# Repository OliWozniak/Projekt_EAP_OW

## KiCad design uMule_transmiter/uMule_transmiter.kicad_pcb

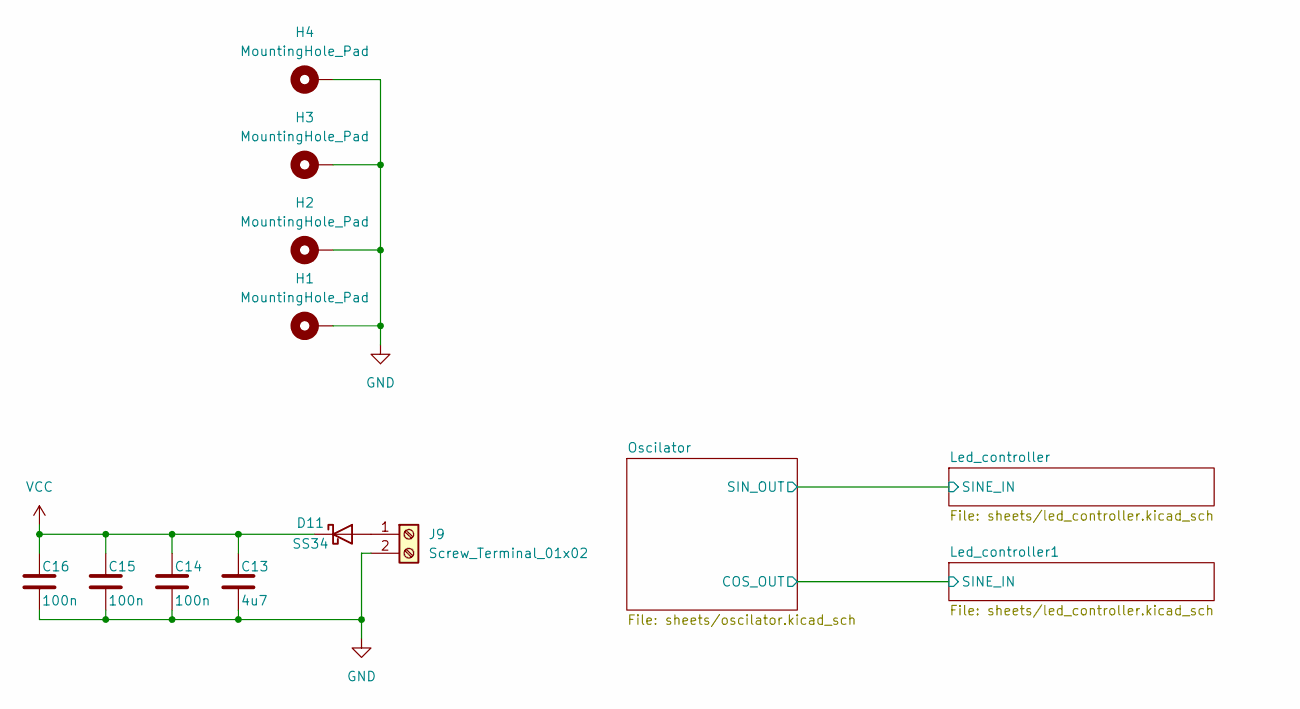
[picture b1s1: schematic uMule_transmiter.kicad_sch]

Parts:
C13: 4u7; C_0805_2012Metric
C14, C15, C16: 100n; C_0603_1608Metric_Pad1.08x0.95mm_HandSolder
D11: SS34; D_SMA
H1, H2, H3, H4: MountingHole_Pad; MountingHole_3.2mm_M3_Pad_Via
J9: Screw_Terminal_01x02; PhoenixContact_MCV_1,5_2-G-3.5_1x02_P3.50mm_Vertical

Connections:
GND: C13.2, C14.2, C15.2, C16.2, H1.1, H2.1, H3.1, H4.1, J9.2; also elsewhere on the board
unnamed: D11.2 (A), J9.1
VCC: C13.1, C14.1, C15.1, C16.1, D11.1 (K); also elsewhere on the board

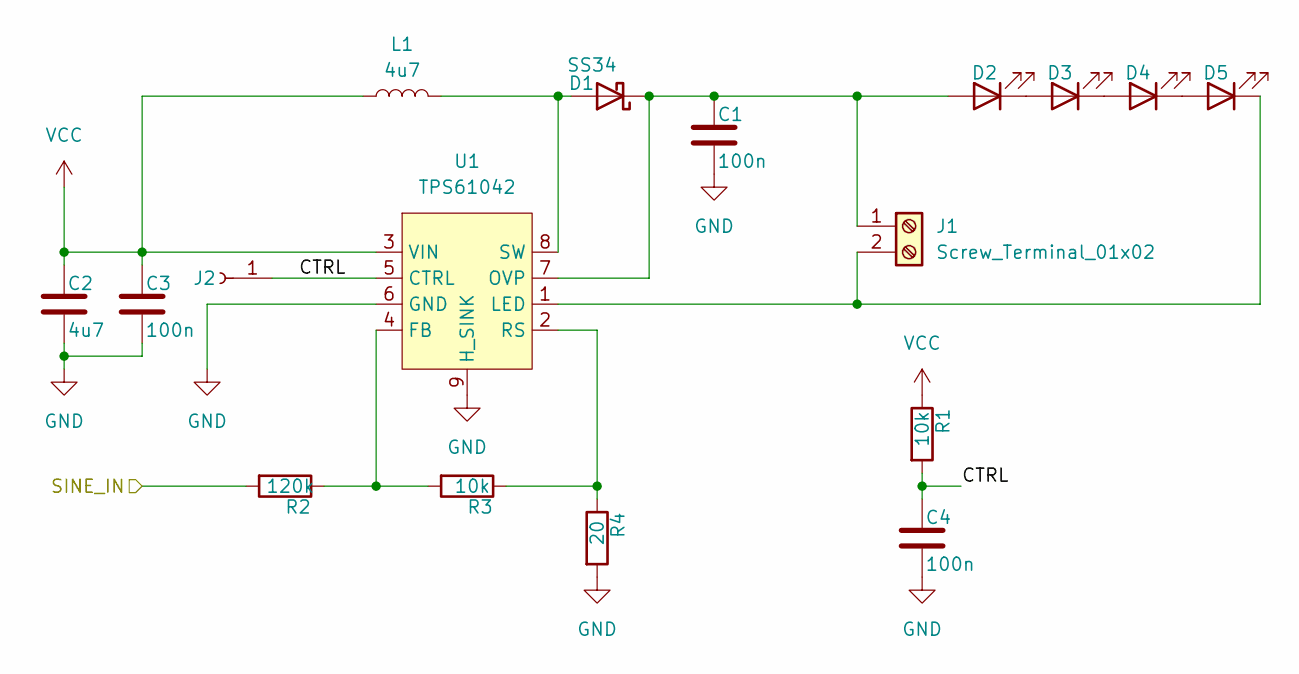
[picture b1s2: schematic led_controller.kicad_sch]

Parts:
C1, C3, C4: 100n; C_0603_1608Metric_Pad1.08x0.95mm_HandSolder
C2: 4u7; C_0805_2012Metric
D1: SS34; D_SMA
D2, D3, D4, D5: LED; LED_D5.0mm
J1: Screw_Terminal_01x02; PhoenixContact_MCV_1,5_2-G-3.5_1x02_P3.50mm_Vertical
J2: Conn_01x01_Socket; PinHeader_1x01_P2.54mm_Vertical
L1: 4u7; L_APV_ANR3015
R1, R3: 10k; R_0603_1608Metric_Pad0.98x0.95mm_HandSolder
R2: 120k; R_0603_1608Metric_Pad0.98x0.95mm_HandSolder
R4: 20; R_1206_3216Metric_Pad1.30x1.75mm_HandSolder
U1: TPS61042; Texas_S-PVSON-N8

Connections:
/Led_controller/CTRL: C4.1, J2.1, R1.2, U1.5 (CTRL)
/Led_controller/SINE_IN: R2.2; also elsewhere on the board
GND: C1.2, C2.2, C3.2, C4.2, R4.2, U1.6 (GND), U1.9 (H_SINK); also elsewhere on the board
unnamed: D1.2 (A), L1.2, U1.8 (SW)
unnamed: C1.1, D1.1 (K), D2.2 (A), J1.1, U1.7 (OVP)
unnamed: D2.1 (K), D3.2 (A)
unnamed: D3.1 (K), D4.2 (A)
unnamed: D4.1 (K), D5.2 (A)
unnamed: D5.1 (K), J1.2, U1.1 (LED)
unnamed: R2.1, R3.2, U1.4 (FB)
unnamed: R3.1, R4.1, U1.2 (RS)
VCC: C2.1, C3.1, L1.1, R1.1, U1.3 (VIN); also elsewhere on the board

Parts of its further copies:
C5, C7, C8: 100n; C_0603_1608Metric_Pad1.08x0.95mm_HandSolder
C6: 4u7; C_0805_2012Metric
D6: SS34; D_SMA
D7, D8, D9, D10: LED; LED_D5.0mm
J3: Screw_Terminal_01x02; PhoenixContact_MCV_1,5_2-G-3.5_1x02_P3.50mm_Vertical
J4: Conn_01x01_Socket; PinHeader_1x01_P2.54mm_Vertical
L2: 4u7; L_APV_ANR3015
R5, R7: 10k; R_0603_1608Metric_Pad0.98x0.95mm_HandSolder
R6: 120k; R_0603_1608Metric_Pad0.98x0.95mm_HandSolder
R8: 20; R_1206_3216Metric_Pad1.30x1.75mm_HandSolder
U2: TPS61042; Texas_S-PVSON-N8

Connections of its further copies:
/Led_controller1/CTRL: C8.1, J4.1, R5.2, U2.5 (CTRL)
/Led_controller1/SINE_IN: R6.2; also elsewhere on the board
GND: C5.2, C6.2, C7.2, C8.2, R8.2, U2.6 (GND), U2.9 (H_SINK); also elsewhere on the board
unnamed: D6.2 (A), L2.2, U2.8 (SW)
unnamed: C5.1, D6.1 (K), D7.2 (A), J3.1, U2.7 (OVP)
unnamed: D7.1 (K), D8.2 (A)
unnamed: D8.1 (K), D9.2 (A)
unnamed: D9.1 (K), D10.2 (A)
unnamed: D10.1 (K), J3.2, U2.1 (LED)
unnamed: R6.1, R7.2, U2.4 (FB)
unnamed: R7.1, R8.1, U2.2 (RS)
VCC: C6.1, C7.1, L2.1, R5.1, U2.3 (VIN); also elsewhere on the board

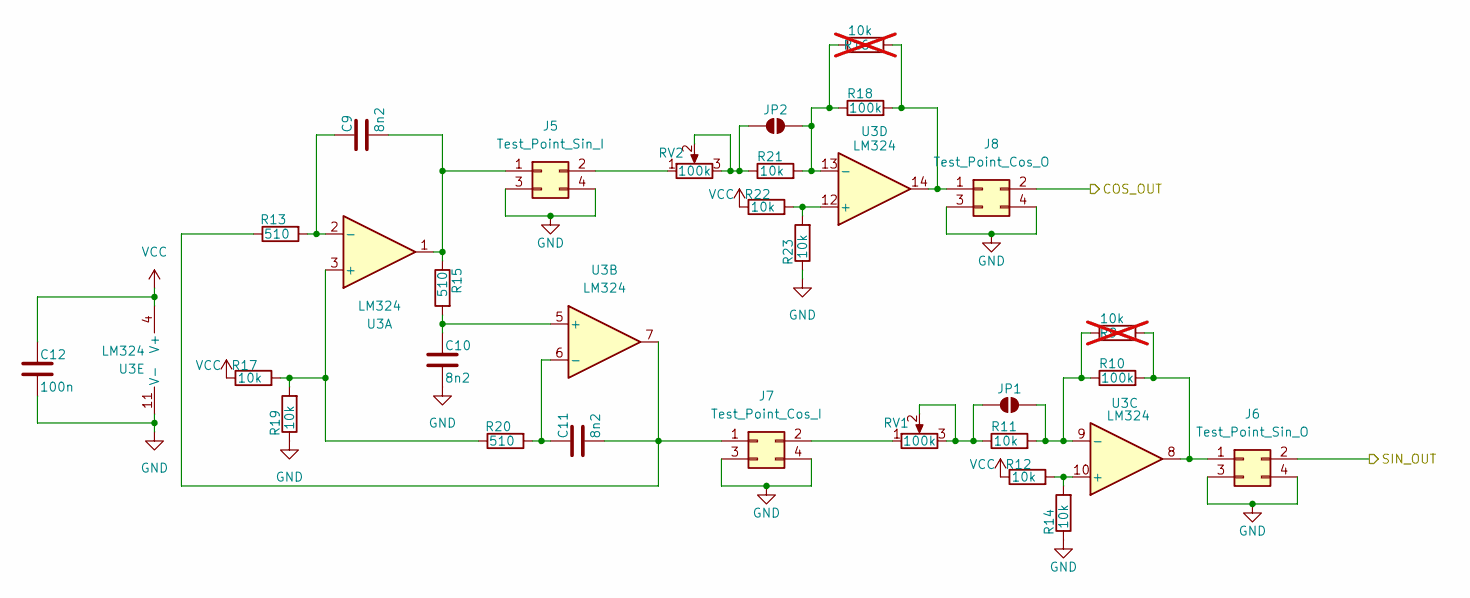
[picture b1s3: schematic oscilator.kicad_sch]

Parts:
C9, C10, C11: 8n2; C_0603_1608Metric_Pad1.08x0.95mm_HandSolder
C12: 100n; C_0603_1608Metric_Pad1.08x0.95mm_HandSolder
J5: Test_Point_Sin_I; PinHeader_2x02_P2.54mm_Vertical
J6: Test_Point_Sin_O; PinHeader_2x02_P2.54mm_Vertical
J7: Test_Point_Cos_I; PinHeader_2x02_P2.54mm_Vertical
J8: Test_Point_Cos_O; PinHeader_2x02_P2.54mm_Vertical
JP1, JP2: SolderJumper_2_Open; SolderJumper-2_P1.3mm_Open_RoundedPad1.0x1.5mm
R9, R16: 10k; R_Axial_DIN0207_L6.3mm_D2.5mm_P7.62mm_Horizontal; not fitted
R10, R18: 100k; R_0603_1608Metric_Pad0.98x0.95mm_HandSolder
R11, R12, R14, R17, R19, R21, R22, R23: 10k; R_0603_1608Metric_Pad0.98x0.95mm_HandSolder
R13, R15, R20: 510; R_0603_1608Metric_Pad0.98x0.95mm_HandSolder
RV1, RV2: 100k; Potentiometer_Bourns_3266Y_Vertical
U3: LM324; SOIC-14_3.9x8.7mm_P1.27mm

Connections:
/Led_controller1/SINE_IN: J8.2; also elsewhere on the board
/Led_controller/SINE_IN: J6.2; also elsewhere on the board
GND: C10.2, C12.2, J5.3, J5.4, J6.3, J6.4, J7.3, J7.4, J8.3, J8.4, R14.1, R19.1, R23.1, U3.11 (V-); also elsewhere on the board
unnamed: C9.2, J5.1, R15.1, U3.1
unnamed: J5.2, RV2.1
unnamed: J6.1, R9.2, R10.2, U3.8
unnamed: C11.2, J7.1, R13.1, U3.7
unnamed: J7.2, RV1.1
unnamed: J8.1, R16.2, R18.2, U3.14
unnamed: JP1.1 (A), R11.1, RV1.2, RV1.3
unnamed: JP1.2 (B), R9.1, R10.1, R11.2, U3.9 (-)
unnamed: JP2.1 (A), R21.1, RV2.2, RV2.3
unnamed: JP2.2 (B), R16.1, R18.1, R21.2, U3.13 (-)
unnamed: R17.2, R19.2, R20.1, U3.3 (+)
unnamed: C9.1, R13.2, U3.2 (-)
unnamed: C10.1, R15.2, U3.5 (+)
unnamed: C11.1, R20.2, U3.6 (-)
unnamed: R12.2, R14.2, U3.10 (+)
unnamed: R22.2, R23.2, U3.12 (+)
VCC: C12.1, R12.1, R17.1, R22.1, U3.4 (V+); also elsewhere on the board

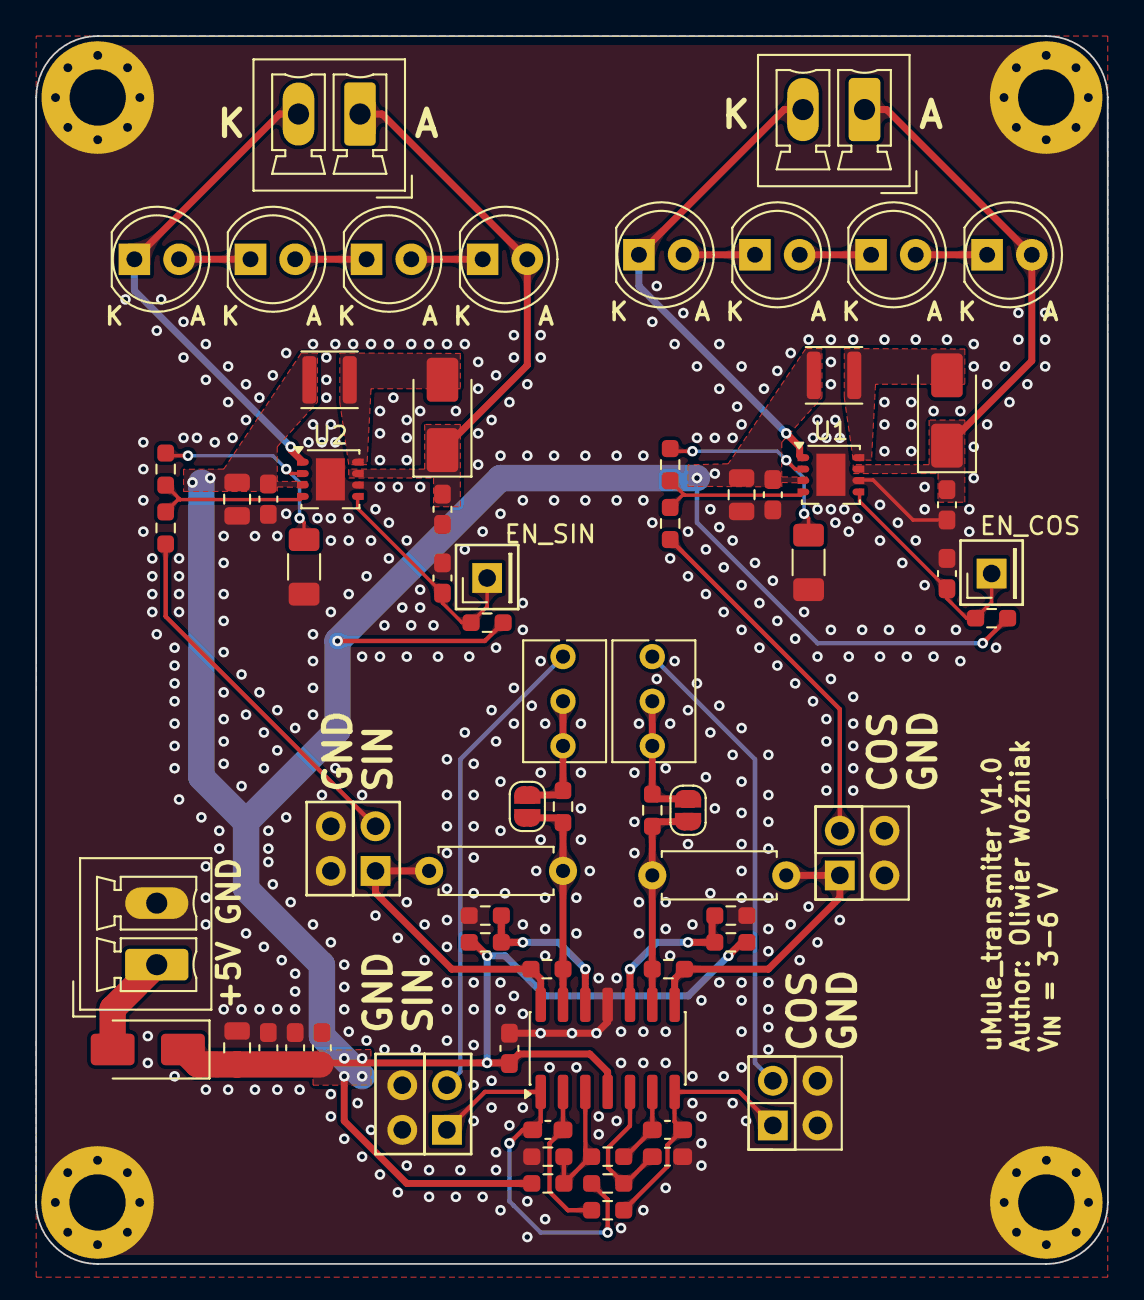
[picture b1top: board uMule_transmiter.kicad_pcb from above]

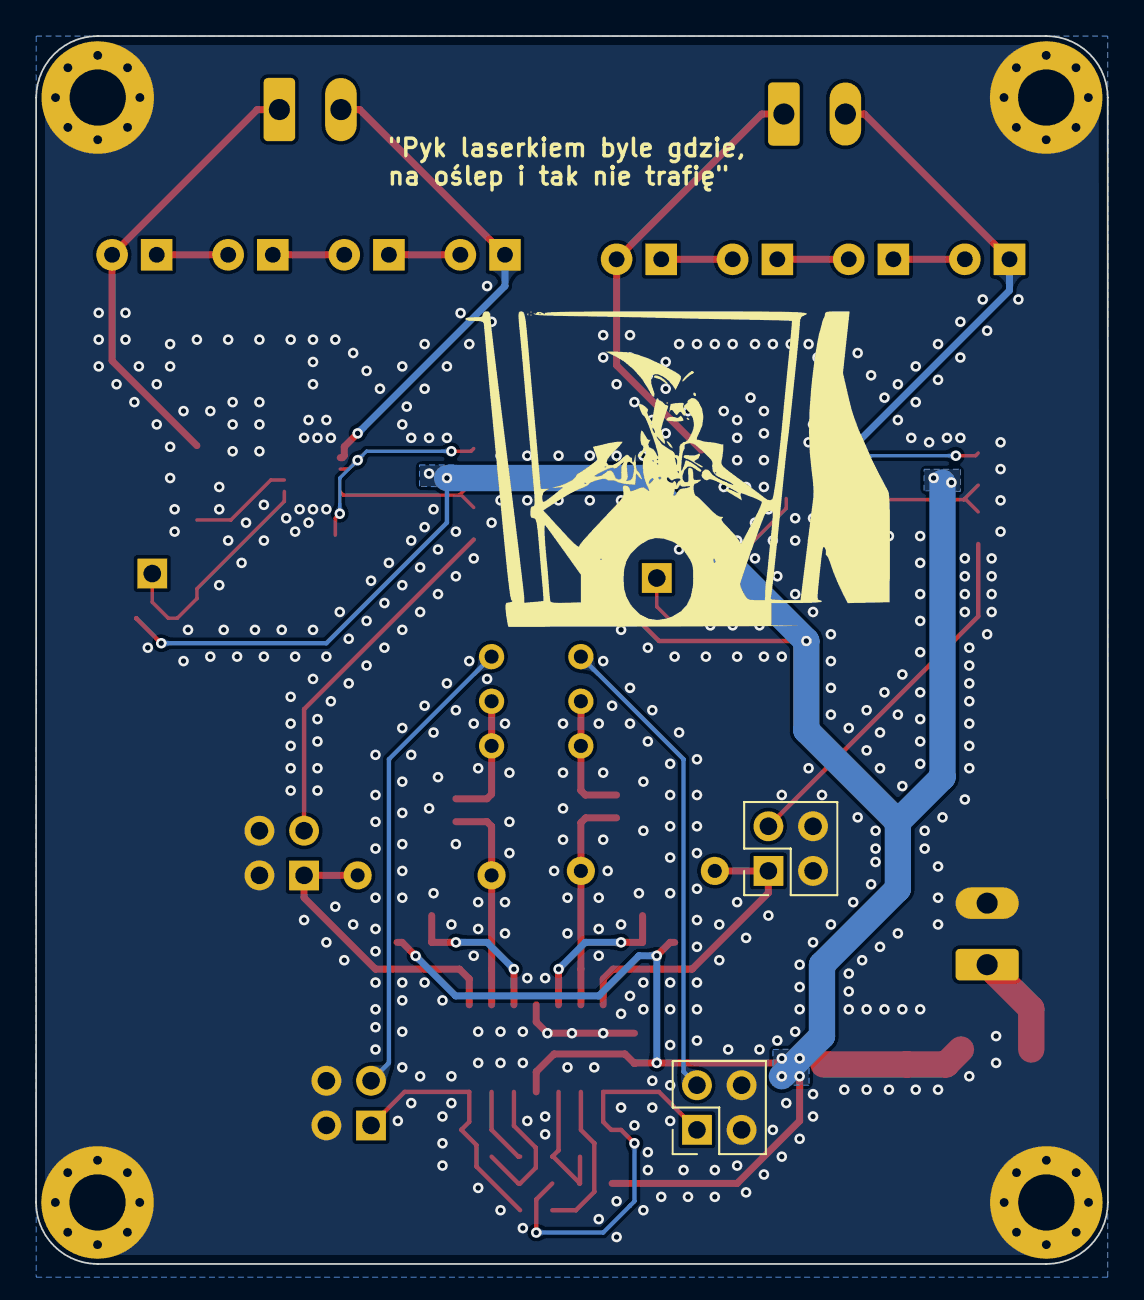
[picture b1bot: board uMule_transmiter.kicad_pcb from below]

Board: 2 copper layers, 61.0 x 69.9 mm, 72 parts (2 on the bottom side), 39 nets.

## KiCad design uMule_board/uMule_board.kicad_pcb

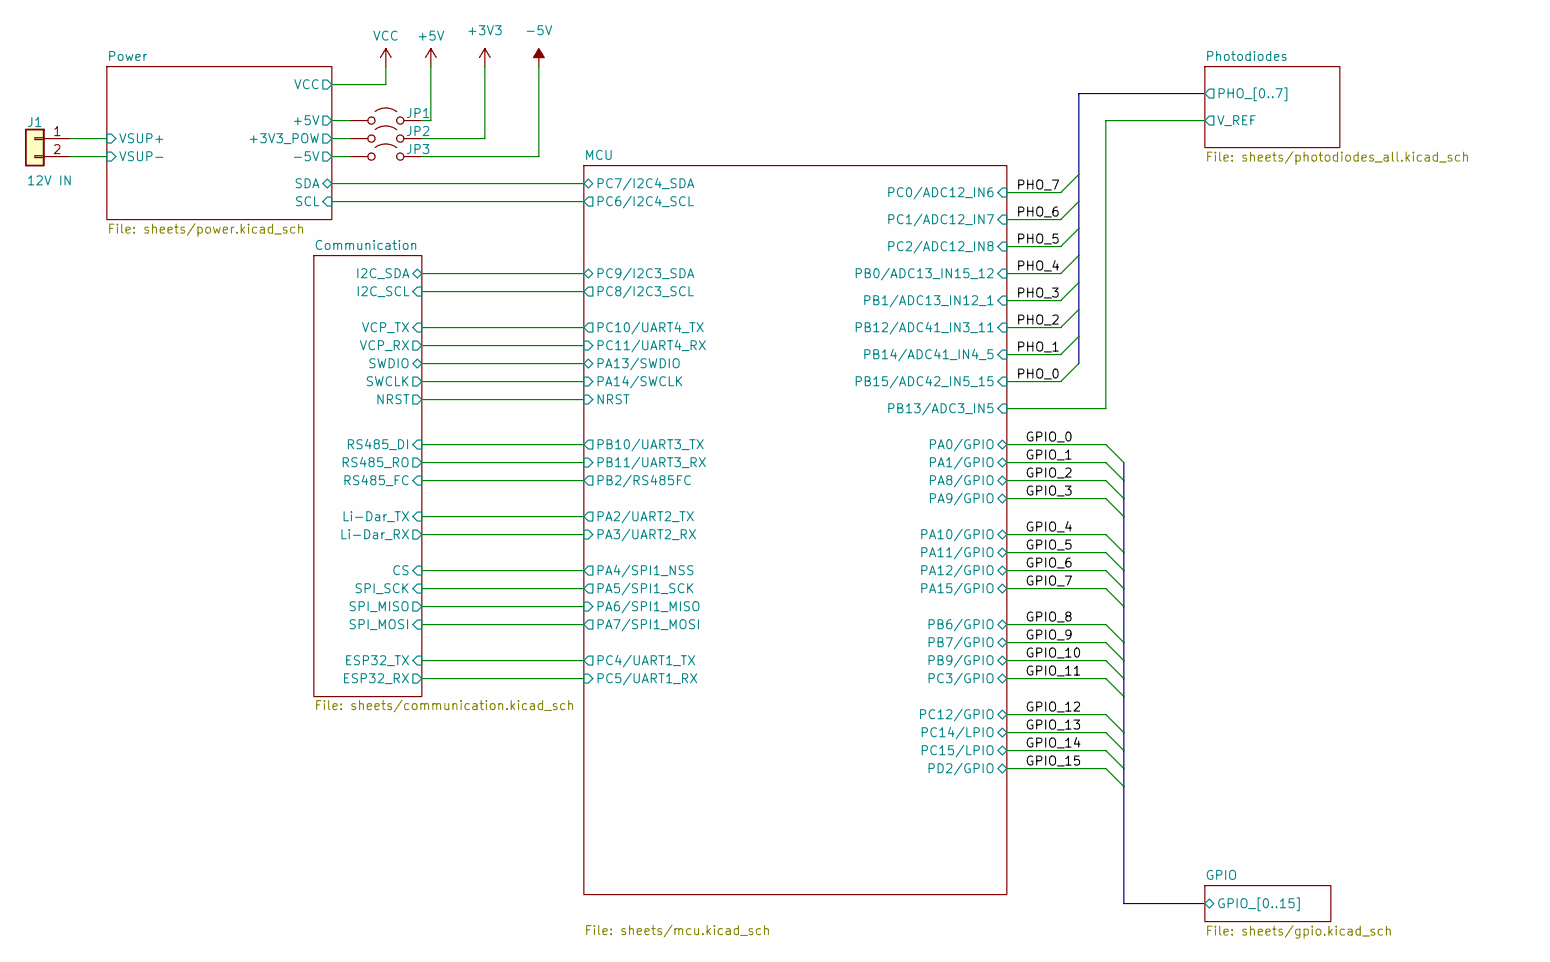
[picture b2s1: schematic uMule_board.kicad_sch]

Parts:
J1: 12V IN; PhoenixContact_MCV_1,5_2-G-3.5_1x02_P3.50mm_Vertical
JP1, JP2, JP3: Jumper_2_Open; TestPoint_2Pads_Pitch2.54mm_Drill0.8mm

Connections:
+3V3: JP2.2 (B); also elsewhere on the board
+5V: JP1.2 (B); also elsewhere on the board
-5V: JP3.2 (B); also elsewhere on the board
/Power/+3V3_POW: JP2.1 (A); also elsewhere on the board
/Power/+5V: JP1.1 (A); also elsewhere on the board
/Power/-5V: JP3.1 (A); also elsewhere on the board
/Power/VSUP+: J1.1; also elsewhere on the board
GND: J1.2; also elsewhere on the board

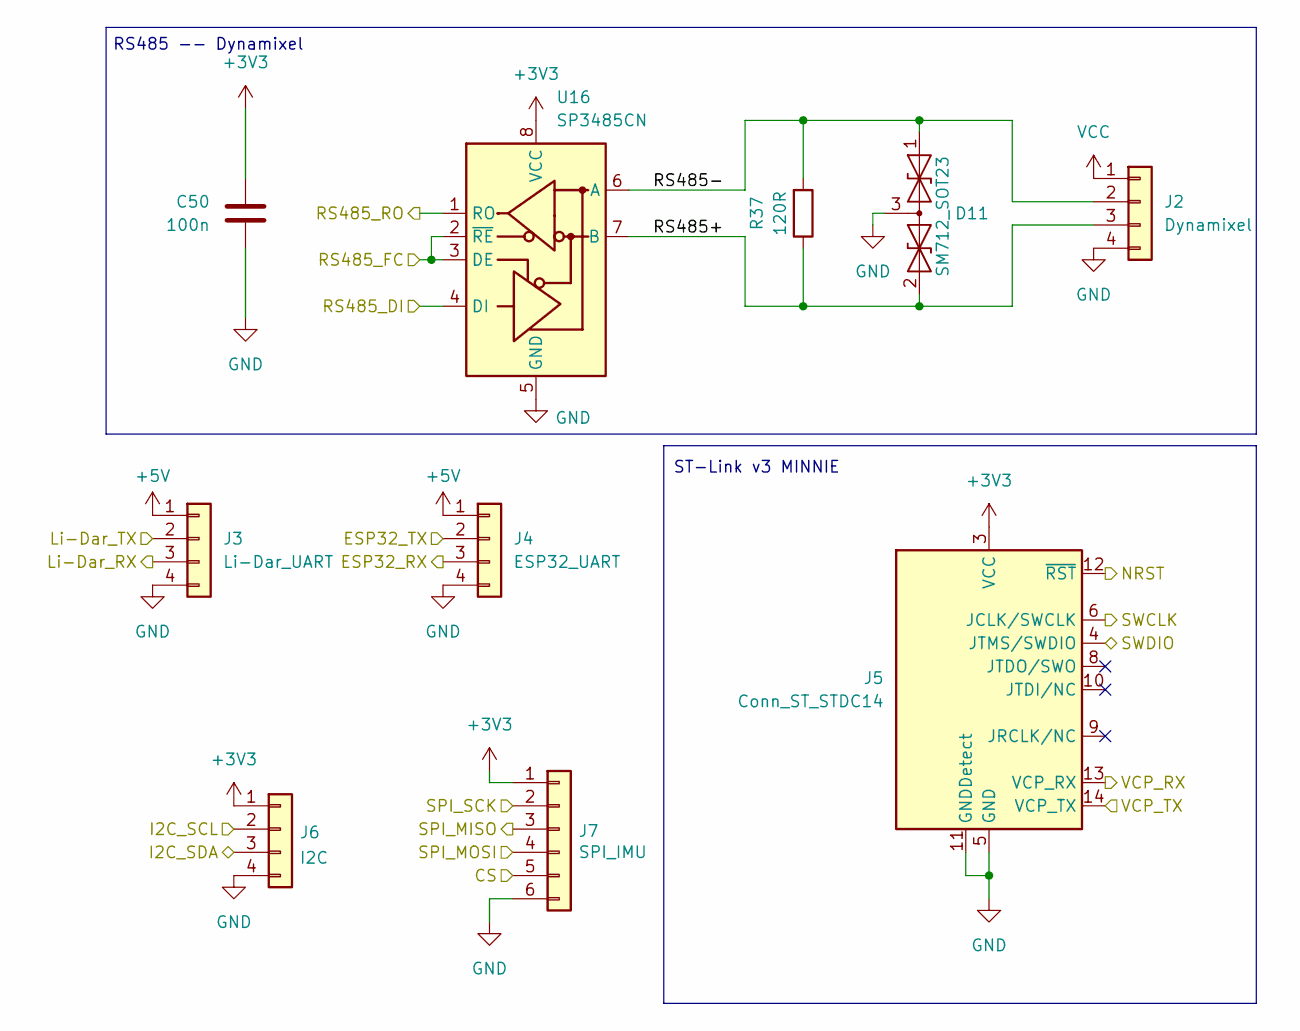
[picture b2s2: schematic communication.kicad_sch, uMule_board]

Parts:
C50: 100n; C_0603_1608Metric
D11: SM712_SOT23; SOT-23
J2: Dynamixel; JST_XH_B4B-XH-A_1x04_P2.50mm_Vertical
J3: Li-Dar_UART; JST_XH_B4B-XH-A_1x04_P2.50mm_Vertical
J4: ESP32_UART; JST_XH_B4B-XH-A_1x04_P2.50mm_Vertical
J5: Conn_ST_STDC14; PinHeader_2x07_P1.27mm_Vertical
J6: I2C; JST_XH_B4B-XH-A_1x04_P2.50mm_Vertical
J7: SPI_IMU; JST_XH_B6B-XH-A_1x06_P2.50mm_Vertical
R37: 120R; R_0603_1608Metric
U16: SP3485CN; SOIC-8_3.9x4.9mm_P1.27mm

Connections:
+3V3: C50.2, J5.3 (VCC), J6.1, J7.1, U16.8 (VCC); also elsewhere on the board
+5V: J3.1, J4.1; also elsewhere on the board
/Communication/CS: J7.5; also elsewhere on the board
/Communication/ESP32_RX: J4.3; also elsewhere on the board
/Communication/ESP32_TX: J4.2; also elsewhere on the board
/Communication/I2C_SCL: J6.2; also elsewhere on the board
/Communication/I2C_SDA: J6.3; also elsewhere on the board
/Communication/Li-Dar_RX: J3.3; also elsewhere on the board
/Communication/Li-Dar_TX: J3.2; also elsewhere on the board
/Communication/RS485+: D11.2 (A2), J2.3, R37.1, U16.7 (B)
/Communication/RS485-: D11.1 (A1), J2.2, R37.2, U16.6 (A)
/Communication/RS485_DI: U16.4 (DI); also elsewhere on the board
/Communication/RS485_FC: U16.2 (~RE), U16.3 (DE); also elsewhere on the board
/Communication/RS485_RO: U16.1 (RO); also elsewhere on the board
/Communication/SPI_MISO: J7.3; also elsewhere on the board
/Communication/SPI_MOSI: J7.4; also elsewhere on the board
/Communication/SPI_SCK: J7.2; also elsewhere on the board
/Communication/SWCLK: J5.6 (JCLK/SWCLK); also elsewhere on the board
/Communication/SWDIO: J5.4 (JTMS/SWDIO); also elsewhere on the board
/Communication/VCP_RX: J5.13 (VCP_RX); also elsewhere on the board
/Communication/VCP_TX: J5.14 (VCP_TX); also elsewhere on the board
/MCU/NRST: J5.12 (~RST); also elsewhere on the board
GND: C50.1, D11.3 (common), J2.4, J3.4, J4.4, J5.5 (GND), J5.7 (GND), J5.11 (GNDDetect), J6.4, J7.6, U16.5 (GND); also elsewhere on the board
VCC: J2.1; also elsewhere on the board

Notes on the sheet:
RS485 -- Dynamixel
ST-Link v3 MINNIE

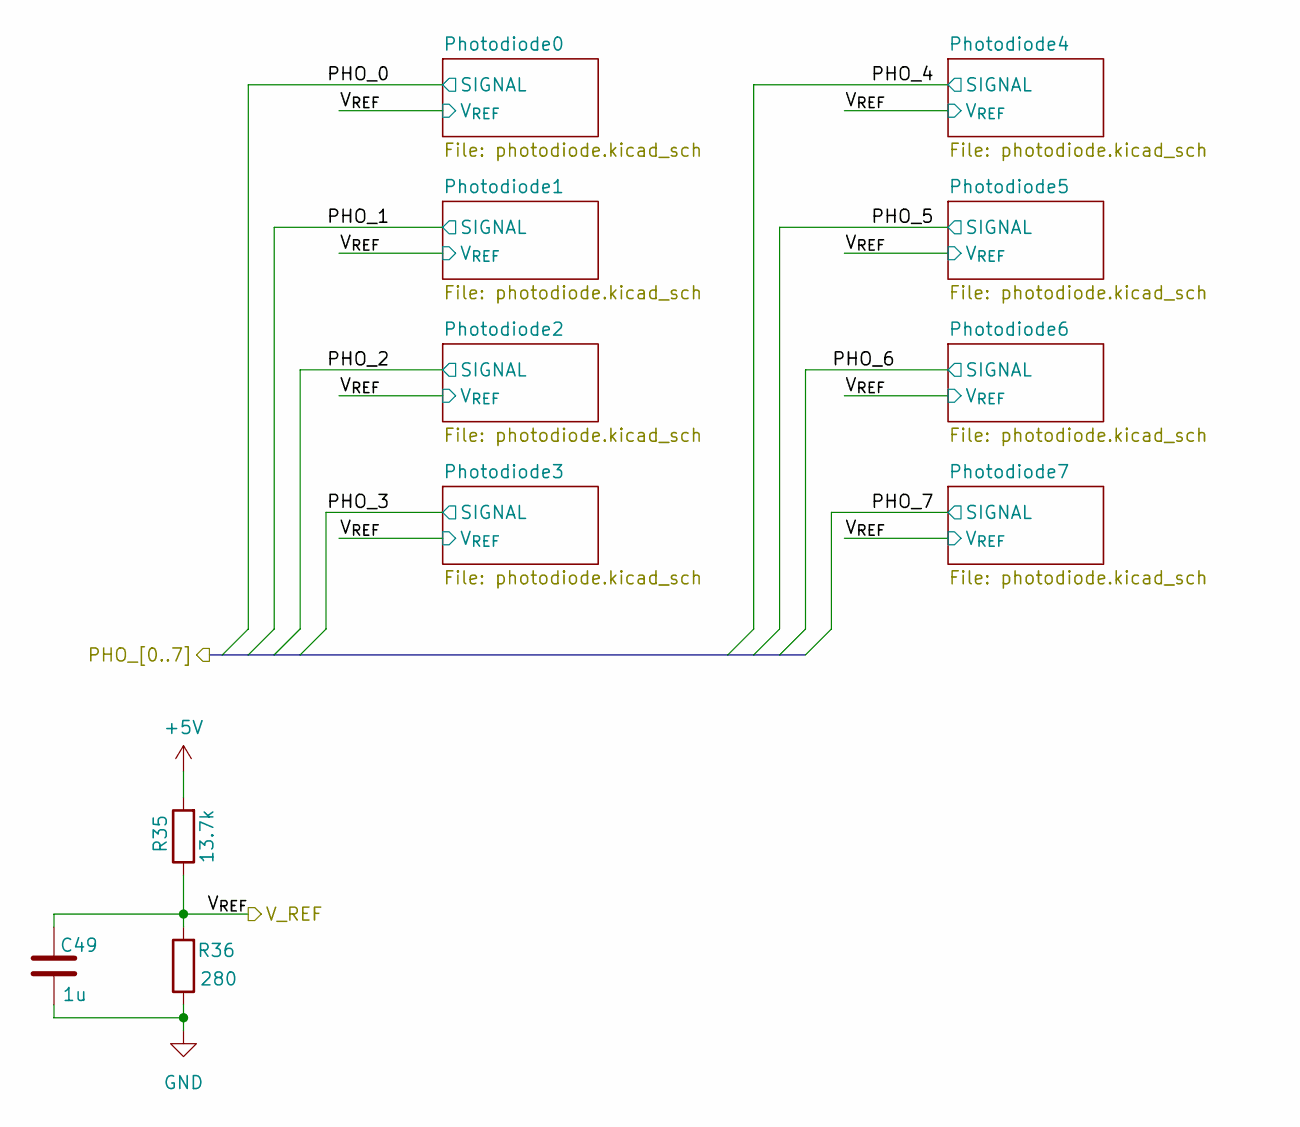
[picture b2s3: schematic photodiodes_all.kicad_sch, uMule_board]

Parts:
C49: 1u; C_0805_2012Metric_Pad1.18x1.45mm_HandSolder
R35: 13.7k; R_0603_1608Metric_Pad0.98x0.95mm_HandSolder
R36: 280; R_0603_1608Metric_Pad0.98x0.95mm_HandSolder

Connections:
+5V: R35.2; also elsewhere on the board
/Photodiodes/V_{REF}: C49.1, R35.1, R36.2; also elsewhere on the board
GND: C49.2, R36.1; also elsewhere on the board

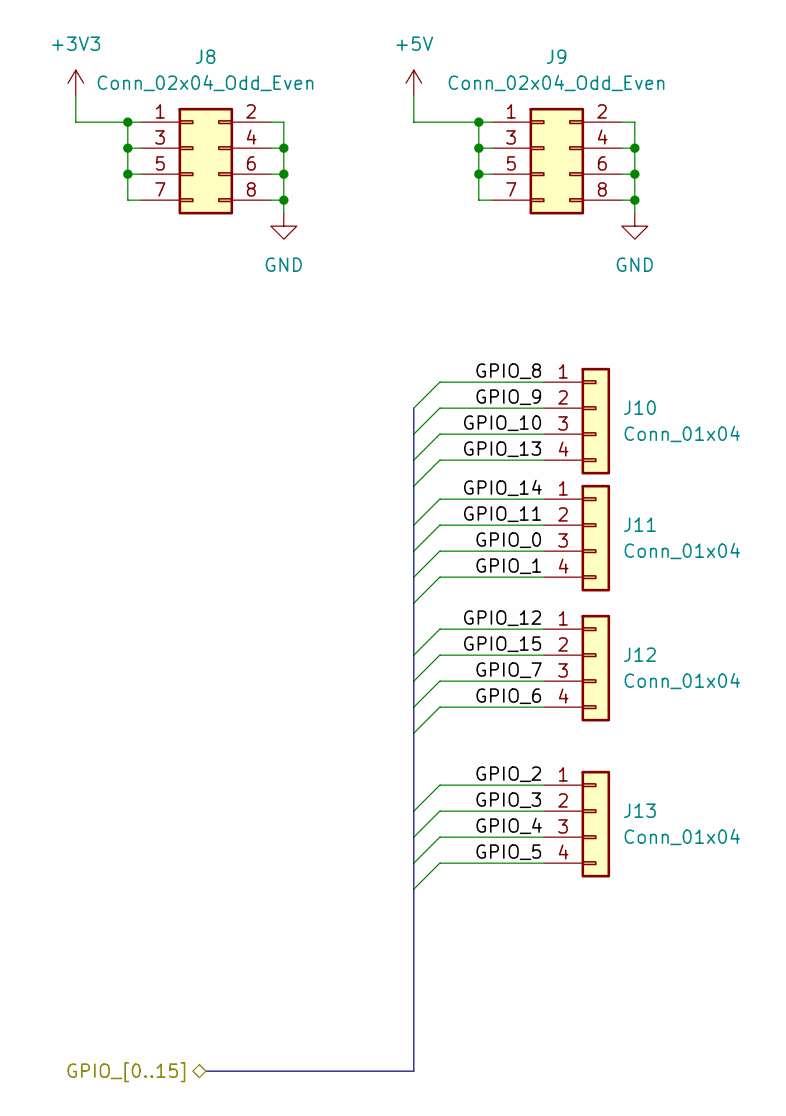
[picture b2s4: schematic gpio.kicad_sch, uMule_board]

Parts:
J8, J9: Conn_02x04_Odd_Even; PinHeader_2x04_P2.54mm_Vertical
J10, J11, J12, J13: Conn_01x04; PinHeader_1x04_P2.54mm_Vertical

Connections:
+3V3: J8.1, J8.3, J8.5, J8.7; also elsewhere on the board
+5V: J9.1, J9.3, J9.5, J9.7; also elsewhere on the board
/GPIO/GPIO_0: J11.3; also elsewhere on the board
/GPIO/GPIO_1: J11.4; also elsewhere on the board
/GPIO/GPIO_2: J13.1; also elsewhere on the board
/GPIO/GPIO_3: J13.2; also elsewhere on the board
/GPIO/GPIO_4: J13.3; also elsewhere on the board
/GPIO/GPIO_5: J13.4; also elsewhere on the board
/GPIO/GPIO_6: J12.4; also elsewhere on the board
/GPIO/GPIO_7: J12.3; also elsewhere on the board
/GPIO/GPIO_8: J10.1; also elsewhere on the board
/GPIO/GPIO_9: J10.2; also elsewhere on the board
/GPIO/GPIO_10: J10.3; also elsewhere on the board
/GPIO/GPIO_11: J11.2; also elsewhere on the board
/GPIO/GPIO_12: J12.1; also elsewhere on the board
/GPIO/GPIO_13: J10.4; also elsewhere on the board
/GPIO/GPIO_14: J11.1; also elsewhere on the board
/GPIO/GPIO_15: J12.2; also elsewhere on the board
GND: J8.2, J8.4, J8.6, J8.8, J9.2, J9.4, J9.6, J9.8; also elsewhere on the board

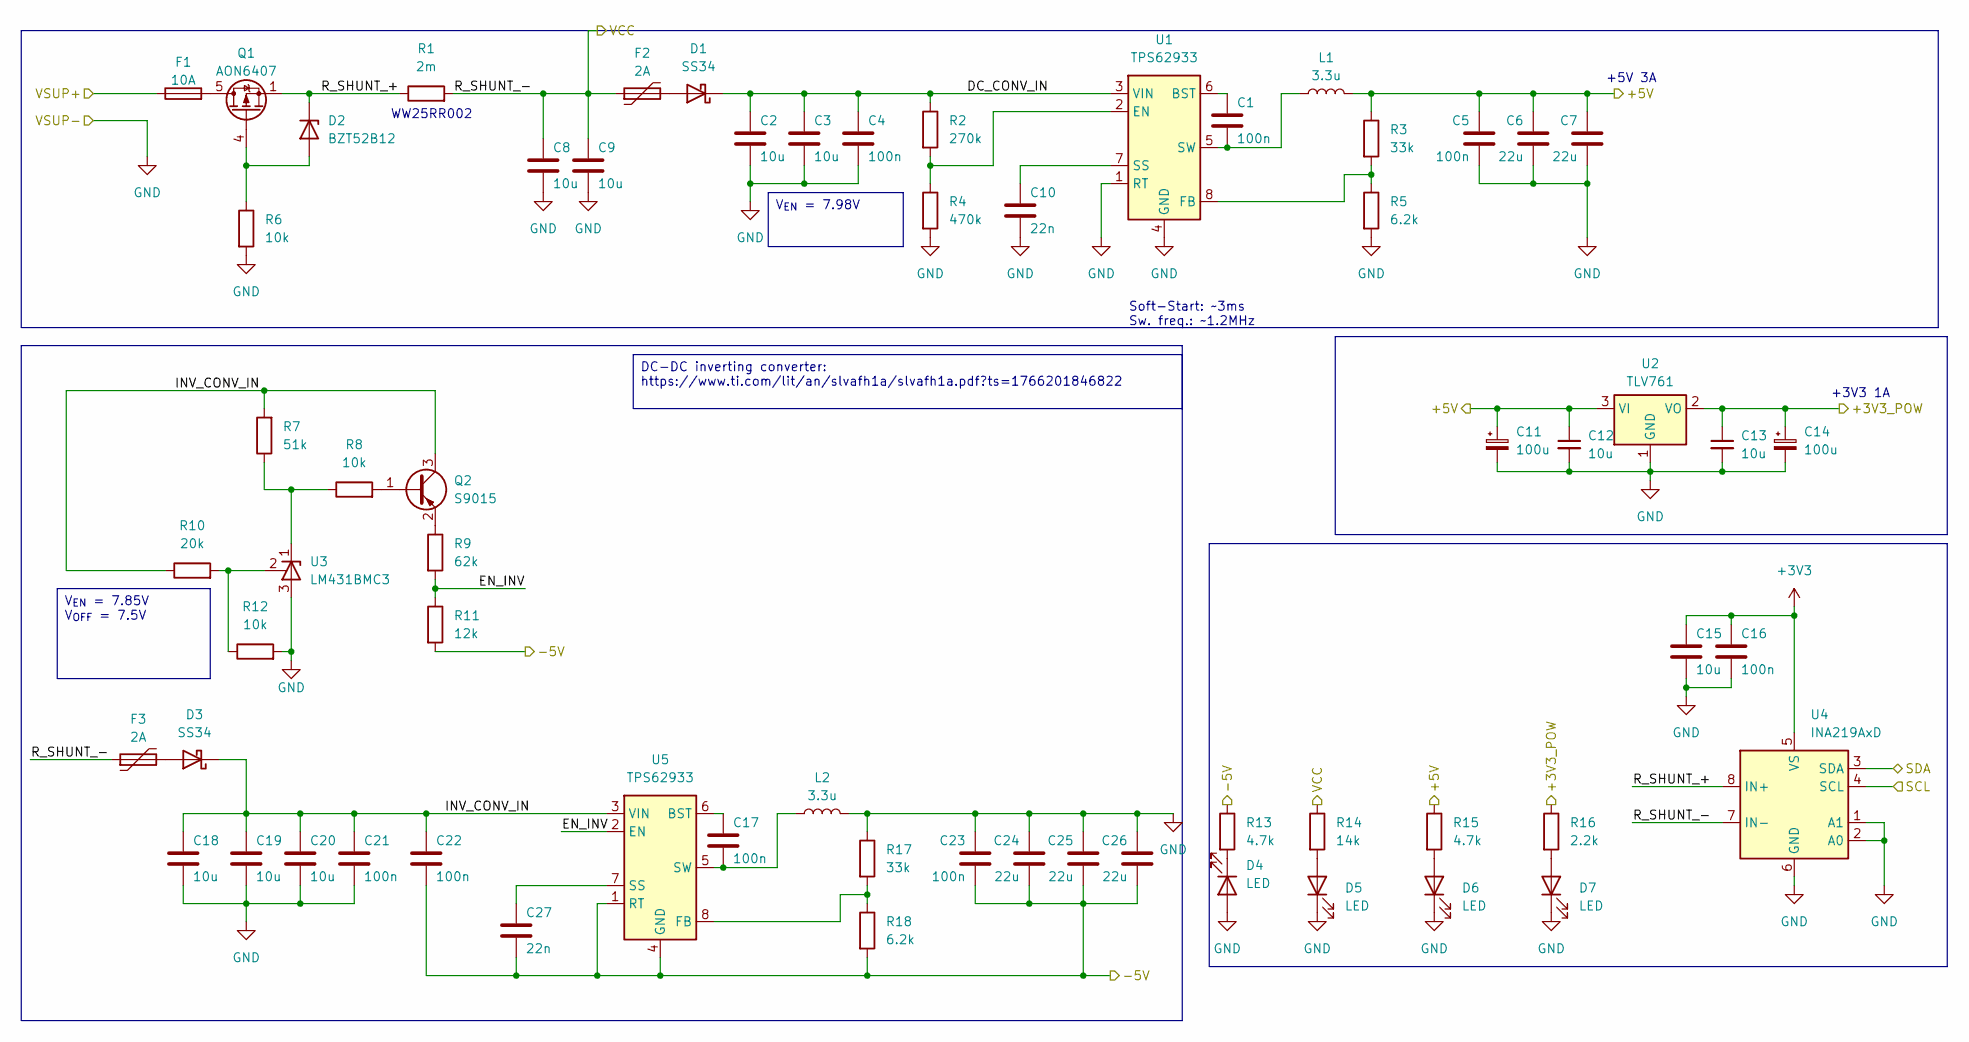
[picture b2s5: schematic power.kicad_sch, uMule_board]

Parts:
C1, C4, C5, C16, C17, C21, C22, C23: 100n; C_0603_1608Metric
C2, C3, C8, C9, C18, C19, C20: 10u; C_0805_2012Metric
C6, C7, C24, C25, C26: 22u; C_0805_2012Metric
C10, C27: 22n; C_0603_1608Metric
C11, C14: 100u; CP_EIA-3528-21_Kemet-B
C12, C13, C15: 10u; C_0603_1608Metric
D1, D3: SS34; D_SMA
D2: BZT52B12; D_SOD-123F
D4, D5, D6, D7: LED; LED_0603_1608Metric_Pad1.05x0.95mm_HandSolder
F1: 10A; Fuseholder_Littelfuse_Nano2_154x
F2, F3: 2A; Fuse_2920_7451Metric
L1, L2: 3.3u; Inductor_TKD_SPM5030VT; jlc C1512760
Q1: AON6407; AO_DFN-8-1EP_5.55x5.2mm_P1.27mm_EP4.12x4.6mm
Q2: S9015; SOT-23
R1: 2m; R_Shunt_2512
R2: 270k; R_0603_1608Metric
R3, R17: 33k; R_0603_1608Metric
R4: 470k; R_0603_1608Metric
R5, R18: 6.2k; R_0603_1608Metric
R6, R8, R12: 10k; R_0603_1608Metric
R7: 51k; R_0603_1608Metric
R9: 62k; R_0603_1608Metric
R10: 20k; R_0603_1608Metric
R11: 12k; R_0603_1608Metric
R13, R15: 4.7k; R_0603_1608Metric
R14: 14k; R_0603_1608Metric
R16: 2.2k; R_0603_1608Metric
U1, U5: TPS62933; SOT-583-8
U2: TLV761; SOT-223-3_TabPin2
U3: LM431BMC3; SOT-23
U4: INA219AxD; SOIC-8_3.9x4.9mm_P1.27mm

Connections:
+3V3: C15.1, C16.1, U4.5 (VS); also elsewhere on the board
/MCU/PC6/I2C4_SCL: U4.4 (SCL); also elsewhere on the board
/MCU/PC7/I2C4_SDA: U4.3 (SDA); also elsewhere on the board
/Power/+3V3_POW: C13.1, C14.1, R16.1, U2.2 (VO); also elsewhere on the board
/Power/+5V: C5.1, C6.1, C7.1, C11.1, C12.1, L1.2, R3.1, R15.1, U2.3 (VI); also elsewhere on the board
/Power/-5V: C22.2, C23.2, C24.2, C25.2, C26.2, C27.2, R11.2, R13.1, R18.2, U5.1 (RT), U5.4 (GND); also elsewhere on the board
/Power/DC_CONV_IN: C2.1, C3.1, C4.1, D1.1 (K), R2.1, U1.3 (VIN)
/Power/EN_INV: R9.2, R11.1, U5.2 (EN)
/Power/INV_CONV_IN: C18.1, C19.1, C20.1, C21.1, C22.1, D3.1 (K), Q2.3 (C), R7.2, R10.1, U5.3 (VIN)
/Power/R_SHUNT_+: D2.1 (K), Q1.1 (S), Q1.2 (S), Q1.3 (S), R1.1, U4.8 (IN+)
/Power/VSUP+: F1.1; also elsewhere on the board
GND: C2.2, C3.2, C4.2, C5.2, C6.2, C7.2, C8.2, C9.2, C10.2, C11.2, C12.2, C13.2, C14.2, C15.2, C16.2, C18.2, C19.2, C20.2, C21.2, C23.1, C24.1, C25.1, C26.1, D4.2 (A), D5.1 (K), D6.1 (K), D7.1 (K), L2.2, R4.2, R5.2, R6.2, R12.2, R17.1, U1.1 (RT), U1.4 (GND), U2.1 (GND), U3.3 (A), U4.1 (A1), U4.2 (A0), U4.6 (GND); also elsewhere on the board
unnamed: D1.2 (A), F2.2
unnamed: D2.2 (A), Q1.4 (G), R6.1
unnamed: D3.2 (A), F3.2
unnamed: D4.1 (K), R13.2
unnamed: D5.2 (A), R14.2
unnamed: D6.2 (A), R15.2
unnamed: D7.2 (A), R16.2
unnamed: F1.2, Q1.5 (D)
unnamed: Q2.1 (B), R8.2
unnamed: Q2.2 (E), R9.1
unnamed: C1.1, U1.6 (BST)
unnamed: R2.2, R4.1, U1.2 (EN)
unnamed: R3.2, R5.1, U1.8 (FB)
unnamed: C10.1, U1.7 (SS)
unnamed: C1.2, L1.1, U1.5 (SW)
unnamed: R7.1, R8.1, U3.1 (K)
unnamed: R10.2, R12.1, U3.2 (REF)
unnamed: C17.1, U5.6 (BST)
unnamed: R17.2, R18.1, U5.8 (FB)
unnamed: C27.1, U5.7 (SS)
unnamed: C17.2, L2.1, U5.5 (SW)
VCC: C8.1, C9.1, F2.1, F3.1, R1.2, R14.1, U4.7 (IN-); also elsewhere on the board

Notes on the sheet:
+3V3 1A
+5V 3A
Soft-Start: ~3ms Sw. freq.: ~1.2MHz
WW25RR002
V_{EN} = 7.85V V_{OFF} = 7.5V
V_{EN} = 7.98V
DC-DC inverting converter: https://www.ti.com/lit/an/slvafh1a/slvafh1a.pdf?ts=1766201846822
